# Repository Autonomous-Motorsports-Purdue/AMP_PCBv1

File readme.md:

PCB Documentation

	- H-bridge
		- An H-bridge is made up of four MOSFETs and four diodes.
		- It switches motor direction based on which two MOSFETs are on.
		- The diodes serve to allow reverse current from the motor to be released.
		- The current solution is Adafruit DRV8871.
			- Its current Limit is 3.6 Amps.
			- This is not enough for the brake Linear Actuator.
		- Recommend switching from DRV8871 to MCP1407.
		- Has peak current capability of 6 A, which is enough for the braking actuator.
		- https://ww1.microchip.com/downloads/en/DeviceDoc/20002019C.pdf
			
	- Steering PWM
		- A square wave is sent to input A of the servo.
		- The pulse width determines position of servo.
		
	- Differential Amplifier 
		- 
		- The formula for a voltage divider is V = VR + (R3/R1)(V1 - V2).
		- The circuit amplifies the difference between the two inputs and adds the voltage VR as an offset.
		- Amplifier for PCB needs to change 0.55 V to 0 V, and  2.75 to 12 volts.
		- Diagram for Reference: https://www.electronicshub.org/wp-content/uploads/2015/01/1.-Differential-amplifier-circuit.jpg
		
	- Braking Linear Actuator
		- 5 Amp Max Current Draw at 12 Volts
		- Duty Cycle: 5 minutes on, 15 minutes off
		- Speed of 1.38 in/s with load of 35 lbs

		Changes
			-C1, C3, C4 backwards footprints (non-polarized capacitors
			-Resistor footprints larger
			-

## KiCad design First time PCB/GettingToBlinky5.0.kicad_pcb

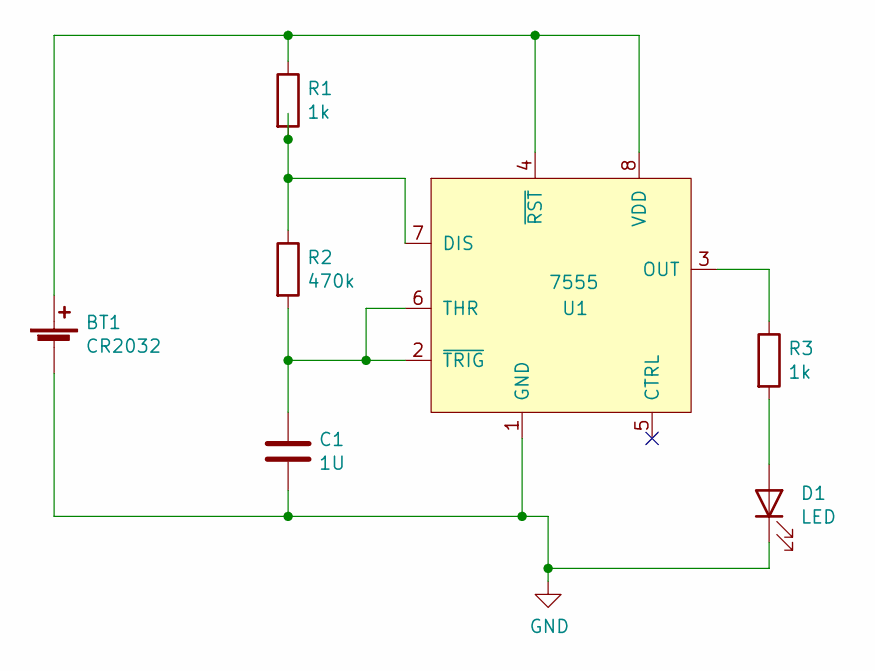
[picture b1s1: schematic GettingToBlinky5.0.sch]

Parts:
BT1: CR2032; S8211-46R
C1: 1U; C_0805_2012Metric_Pad1.15x1.40mm_HandSolder
D1: LED; LED_0805_2012Metric_Pad1.15x1.40mm_HandSolder
R1, R3: 1k; R_0805_2012Metric_Pad1.15x1.40mm_HandSolder
R2: 470k; R_0805_2012Metric_Pad1.15x1.40mm_HandSolder
U1: 7555; SOIC-8_3.9x4.9mm_P1.27mm

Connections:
GND: BT1.2 (-), C1.2, D1.1 (K), U1.1 (GND)
unnamed: BT1.1 (+), R1.1, U1.4 (~RST), U1.8 (VDD)
unnamed: C1.1, R2.2, U1.2 (~TRIG), U1.6 (THR)
unnamed: D1.2 (A), R3.2
unnamed: R1.2, R2.1, U1.7 (DIS)
unnamed: R3.1, U1.3 (OUT)

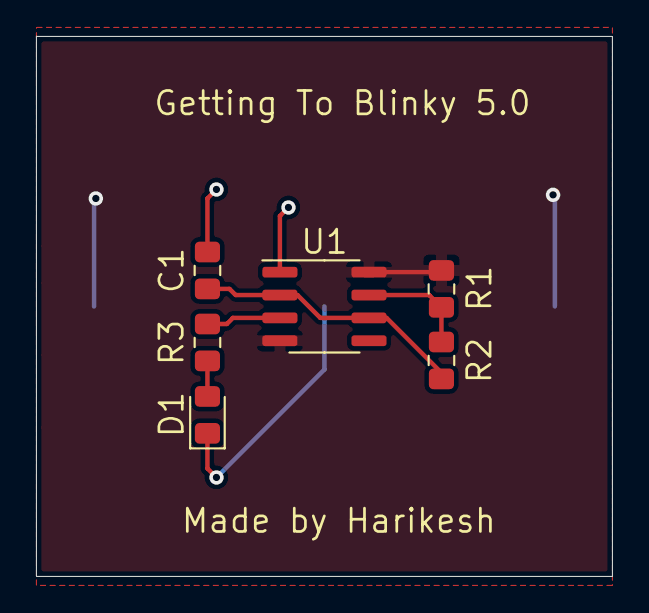
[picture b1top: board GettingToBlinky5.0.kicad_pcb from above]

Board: 2 copper layers, 32.0 x 30.0 mm, 7 parts (1 on the bottom side), 6 nets.

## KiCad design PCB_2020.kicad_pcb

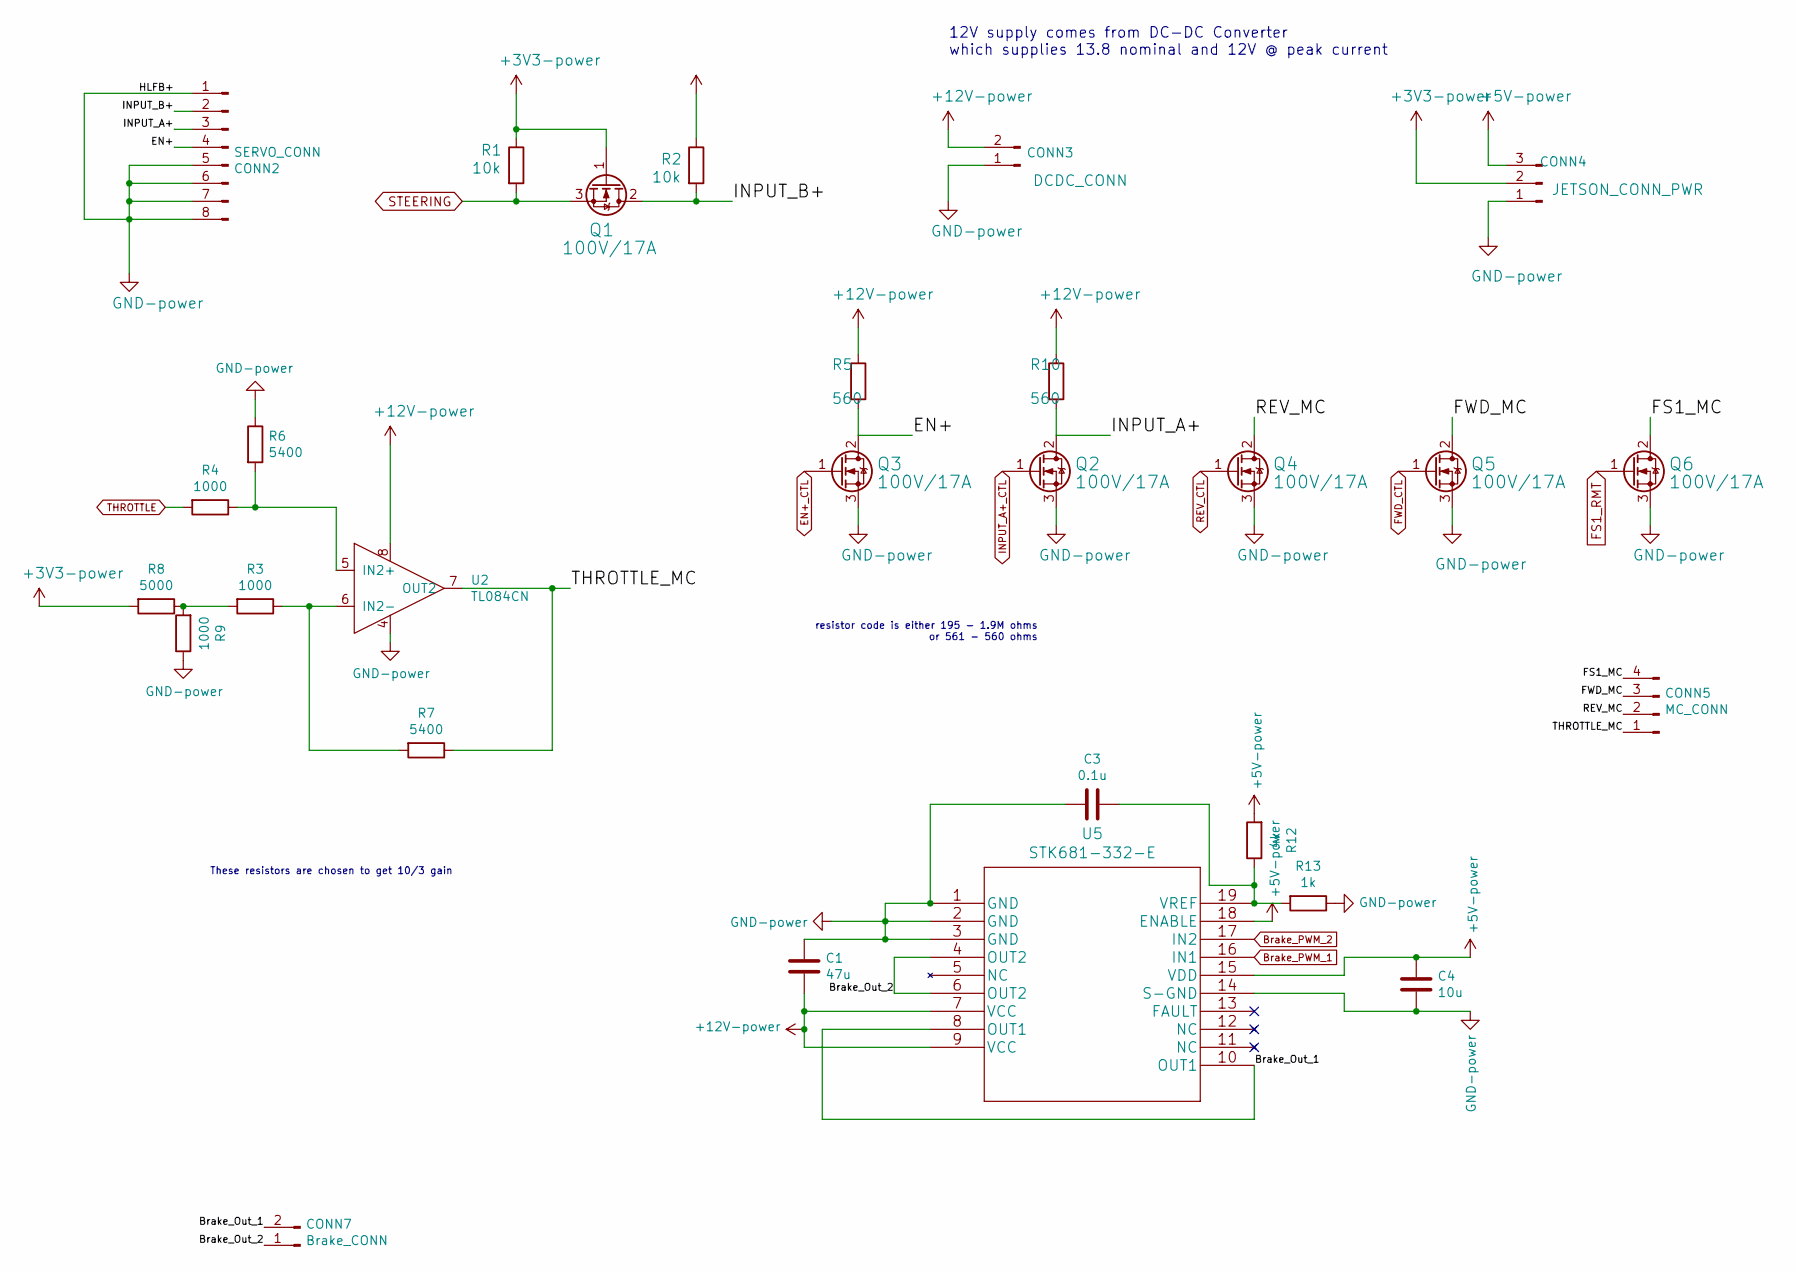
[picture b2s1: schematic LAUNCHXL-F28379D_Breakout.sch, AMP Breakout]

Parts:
C1: 47u; C_Radial_D4.0mm_H5.0mm_P1.50mm
C3: 0.1u; CP_Radial_D4.0mm_P1.50mm
C4: 10u; CP_Radial_D4.0mm_P1.50mm
CONN2: SERVO_CONN; Molex_Mini-Fit_Jr_5566-08A_2x04_P4.20mm_Vertical
CONN5: MC_CONN; Molex_KK-254_AE-6410-04A_1x04_P2.54mm_Vertical
CONN7: Brake_CONN; Molex_Mini-Fit_Jr_5566-02A_2x01_P4.20mm_Vertical
DCDC_CONN_12V: DCDC_CONN; Molex_Mini-Fit_Jr_5566-02A_2x01_P4.20mm_Vertical
JETSON_CONN_PWR: JETSON_CONN_PWR; Molex_KK-254_AE-6410-03A_1x03_P2.54mm_Vertical
Q1, Q2, Q3, Q4, Q5, Q6: 100V/17A; TO-220-3_Vertical
R1, R2: 10k; R_Axial_DIN0204_L3.6mm_D1.6mm_P7.62mm_Horizontal
R3, R4, R9: 1000; R_Axial_DIN0204_L3.6mm_D1.6mm_P7.62mm_Horizontal
R5, R18: 560; R_Axial_DIN0204_L3.6mm_D1.6mm_P7.62mm_Horizontal
R6, R7: 5400; R_Axial_DIN0204_L3.6mm_D1.6mm_P7.62mm_Horizontal
R8: 5000; R_Axial_DIN0204_L3.6mm_D1.6mm_P7.62mm_Horizontal
R12: 4k; R_Axial_DIN0204_L3.6mm_D1.6mm_P7.62mm_Horizontal
R13: 1k; R_Axial_DIN0204_L3.6mm_D1.6mm_P7.62mm_Horizontal
U2: TL084CN
U5: STK681-332-E

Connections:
+3V3: Q1.1 (G), R1.1, R8.2; also elsewhere on the board
+5V: C4.2, R12.2, U5.15 (VDD), U5.18 (ENABLE); also elsewhere on the board
+12V: C1.1, R2.1, R5.1, U2.8, U5.7 (VCC), U5.9 (VCC); also elsewhere on the board
/LAUNCHXL-F28379D Breakout/Brake_Out_1: CONN7.2, U5.8 (OUT1), U5.10 (OUT1)
/LAUNCHXL-F28379D Breakout/Brake_Out_2: CONN7.1, U5.4 (OUT2), U5.6 (OUT2)
/LAUNCHXL-F28379D Breakout/EN+: CONN2.4, Q3.2 (D), R5.2
/LAUNCHXL-F28379D Breakout/FS1_MC: CONN5.4, Q6.2 (D)
/LAUNCHXL-F28379D Breakout/FWD_MC: CONN5.3, Q5.2 (D)
/LAUNCHXL-F28379D Breakout/INPUT_A+: CONN2.3, Q2.2 (D); also elsewhere on the board
/LAUNCHXL-F28379D Breakout/INPUT_B+: CONN2.2, Q1.2 (D), R2.2
/LAUNCHXL-F28379D Breakout/REV_MC: CONN5.2, Q4.2 (D)
/LAUNCHXL-F28379D Breakout/THROTTLE_MC: CONN5.1, R7.1, U2.7 (OUT2)
Brake_PWM_1: U5.16 (IN1); also elsewhere on the board
Brake_PWM_2: U5.17 (IN2); also elsewhere on the board
EN+_CTL: Q3.1 (G); also elsewhere on the board
FS1_RMT: Q6.1 (G); also elsewhere on the board
FWD_CTL: Q5.1 (G); also elsewhere on the board
GND: C1.2, C3.1, C4.1, CONN2.1, CONN2.5, CONN2.6, CONN2.7, CONN2.8, Q2.3 (S), Q3.3 (S), Q4.3 (S), Q5.3 (S), Q6.3 (S), R6.1, R9.1, R13.1, U2.4, U5.1 (GND), U5.2 (GND), U5.3 (GND), U5.14 (S-GND); also elsewhere on the board
INPUT_A+_CTL: Q2.1 (G); also elsewhere on the board
unnamed: C3.2, R12.1, R13.2, U5.19 (VREF)
unnamed: R3.1, R7.2, U2.6 (IN2-)
unnamed: R3.2, R8.1, R9.2
unnamed: R4.1, R6.2, U2.5 (IN2+)
REV_CTL: Q4.1 (G); also elsewhere on the board
STEERING: Q1.3 (S), R1.2; also elsewhere on the board
THROTTLE: R4.2; also elsewhere on the board

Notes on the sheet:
12V supply comes from DC-DC Converter which supplies 13.8 nominal and 12V @ peak current
resistor code is either 195 - 1.9M ohms or 561 - 560 ohms
These resistors are chosen to get 10/3 gain

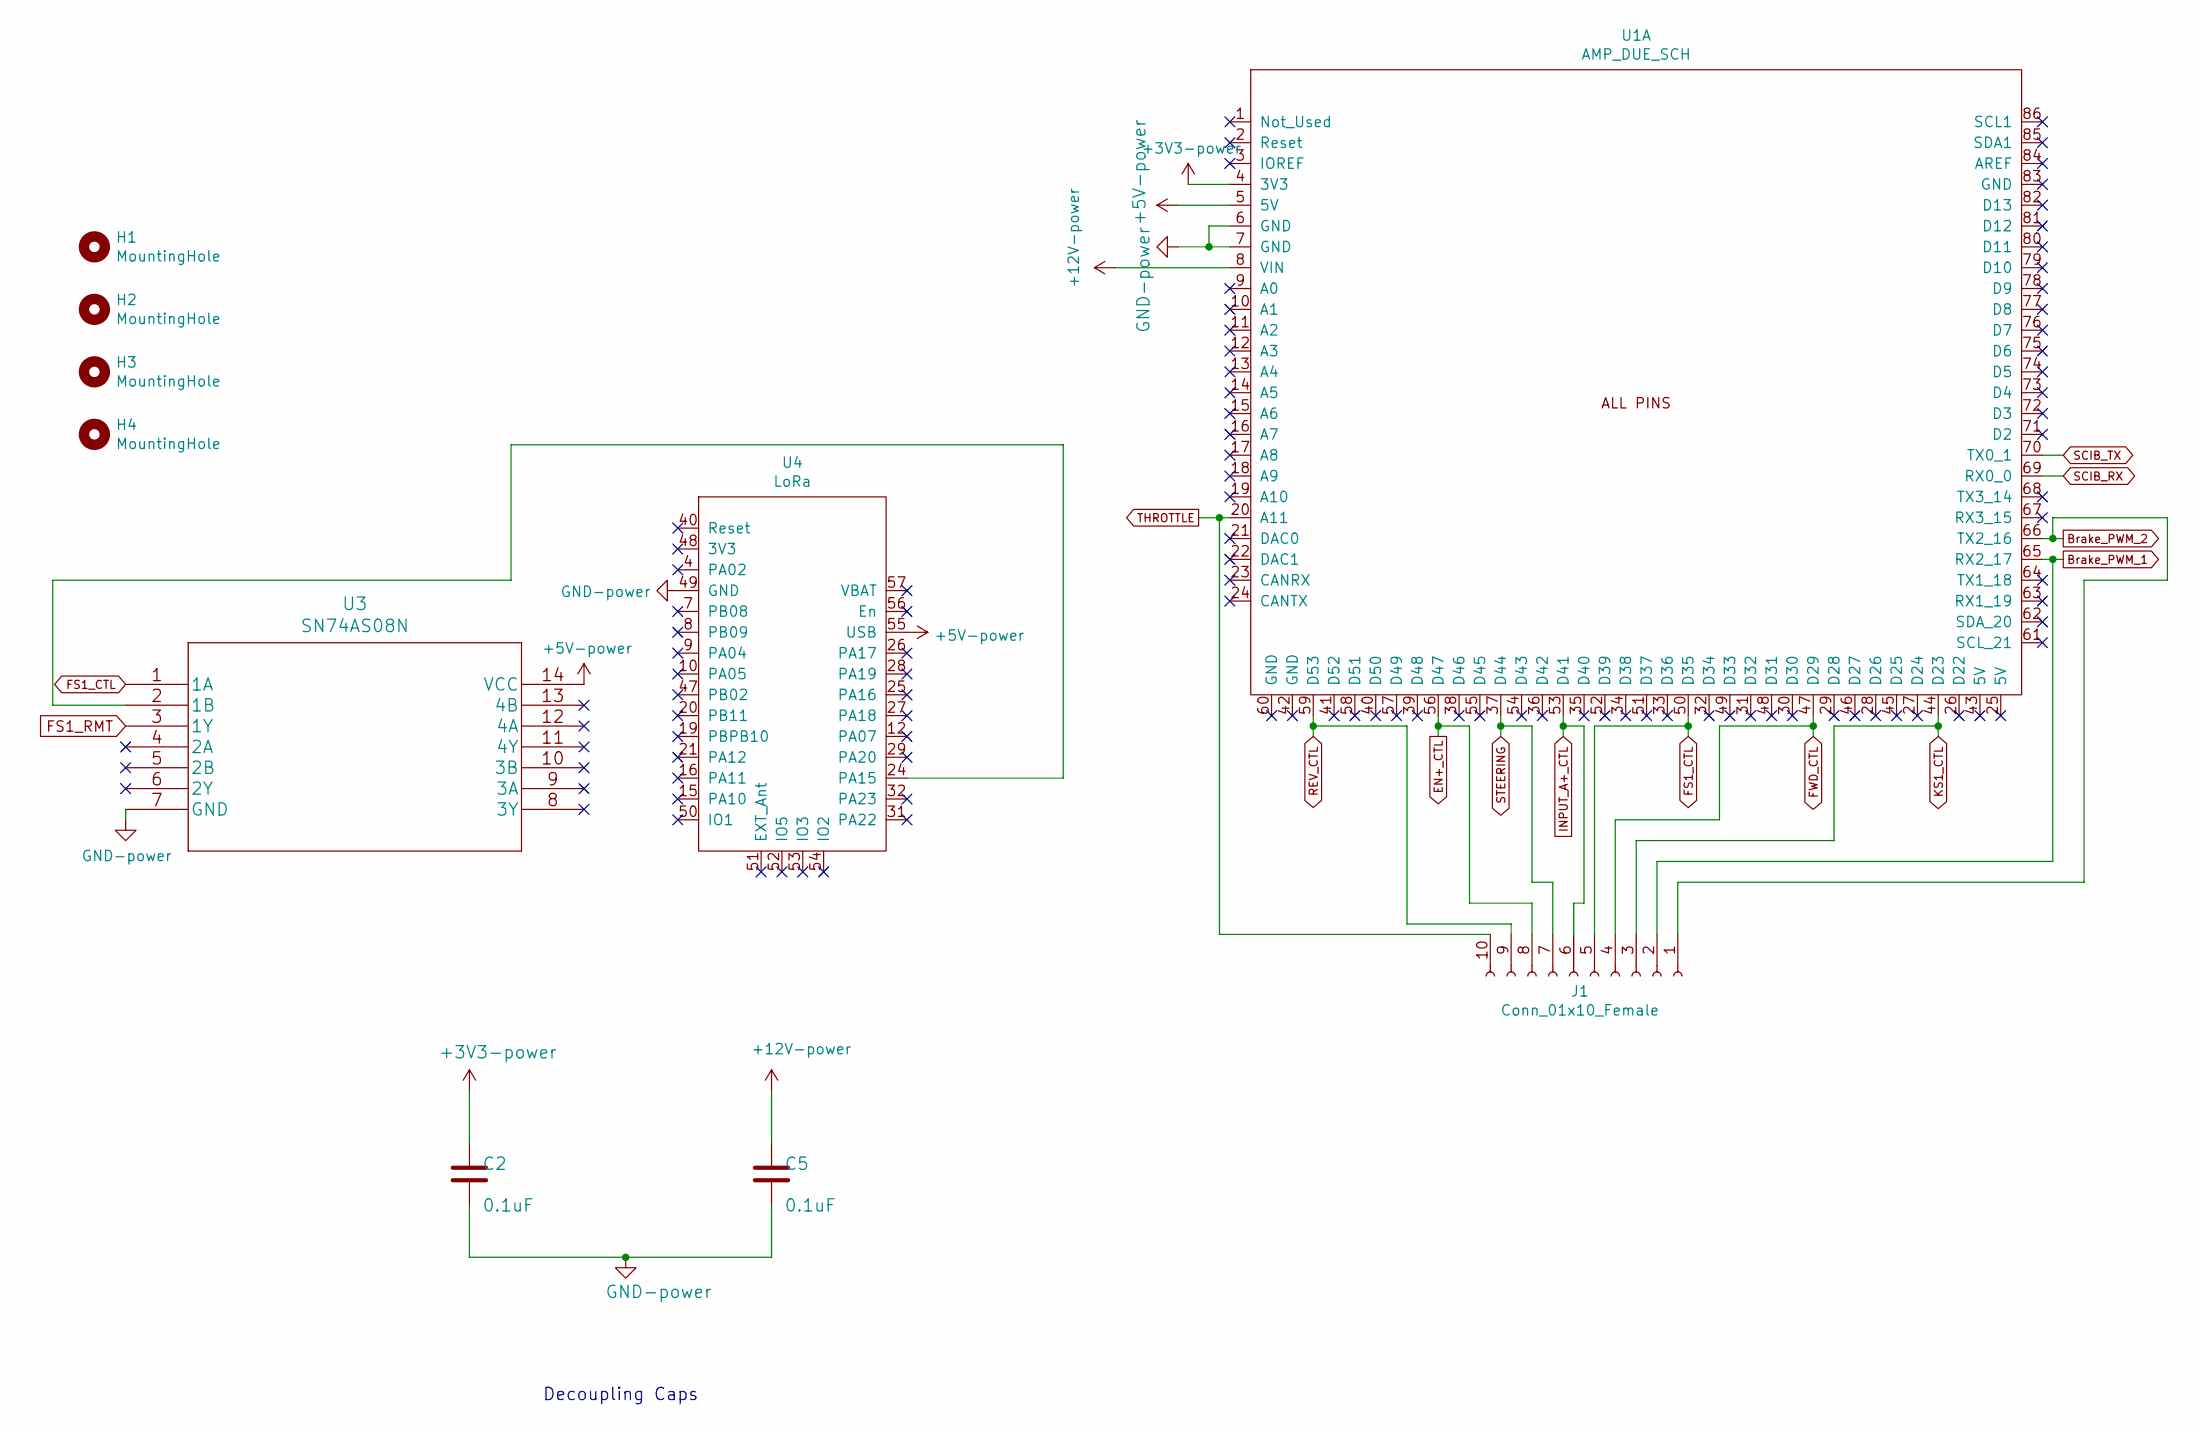
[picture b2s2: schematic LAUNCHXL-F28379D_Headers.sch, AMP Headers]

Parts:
C2, C5: 0.1uF; CP_Radial_D4.0mm_P1.50mm
H1, H2, H3, H4: MountingHole; MountingHole_2.7mm
J1: Conn_01x10_Female; Molex_Mini-Fit_Jr_5566-10A2_2x05_P4.20mm_Vertical
U1: AMP_DUE_SCH; Arduino DUE
U3: SN74AS08N
U4: LoRa

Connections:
+3V3: C2.1, U1.4 (3V3); also elsewhere on the board
+5V: U1.5 (5V), U3.14 (VCC), U4.55 (USB); also elsewhere on the board
+12V: C5.1, U1.8 (VIN); also elsewhere on the board
Brake_PWM_1: J1.2, U1.65 (RX2_17); also elsewhere on the board
Brake_PWM_2: J1.1, U1.66 (TX2_16); also elsewhere on the board
EN+_CTL: J1.8, U1.56 (D47); also elsewhere on the board
FS1_CTL: J1.5, U1.50 (D35), U3.1 (1A)
FS1_RMT: U3.3 (1Y); also elsewhere on the board
FWD_CTL: J1.4, U1.47 (D29); also elsewhere on the board
GND: C2.2, C5.2, U1.6 (GND), U1.7 (GND), U3.7 (GND), U4.49 (GND); also elsewhere on the board
INPUT_A+_CTL: J1.6, U1.53 (D41); also elsewhere on the board
KS1_CTL: J1.3, U1.44 (D23)
unnamed: U3.2 (1B), U4.24 (PA15)
REV_CTL: J1.9, U1.59 (D53); also elsewhere on the board
SCIB_RX: U1.69 (RX0_0)
SCIB_TX: U1.70 (TX0_1)
STEERING: J1.7, U1.37 (D44); also elsewhere on the board
THROTTLE: J1.10, U1.20 (A11); also elsewhere on the board

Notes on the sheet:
Decoupling Caps

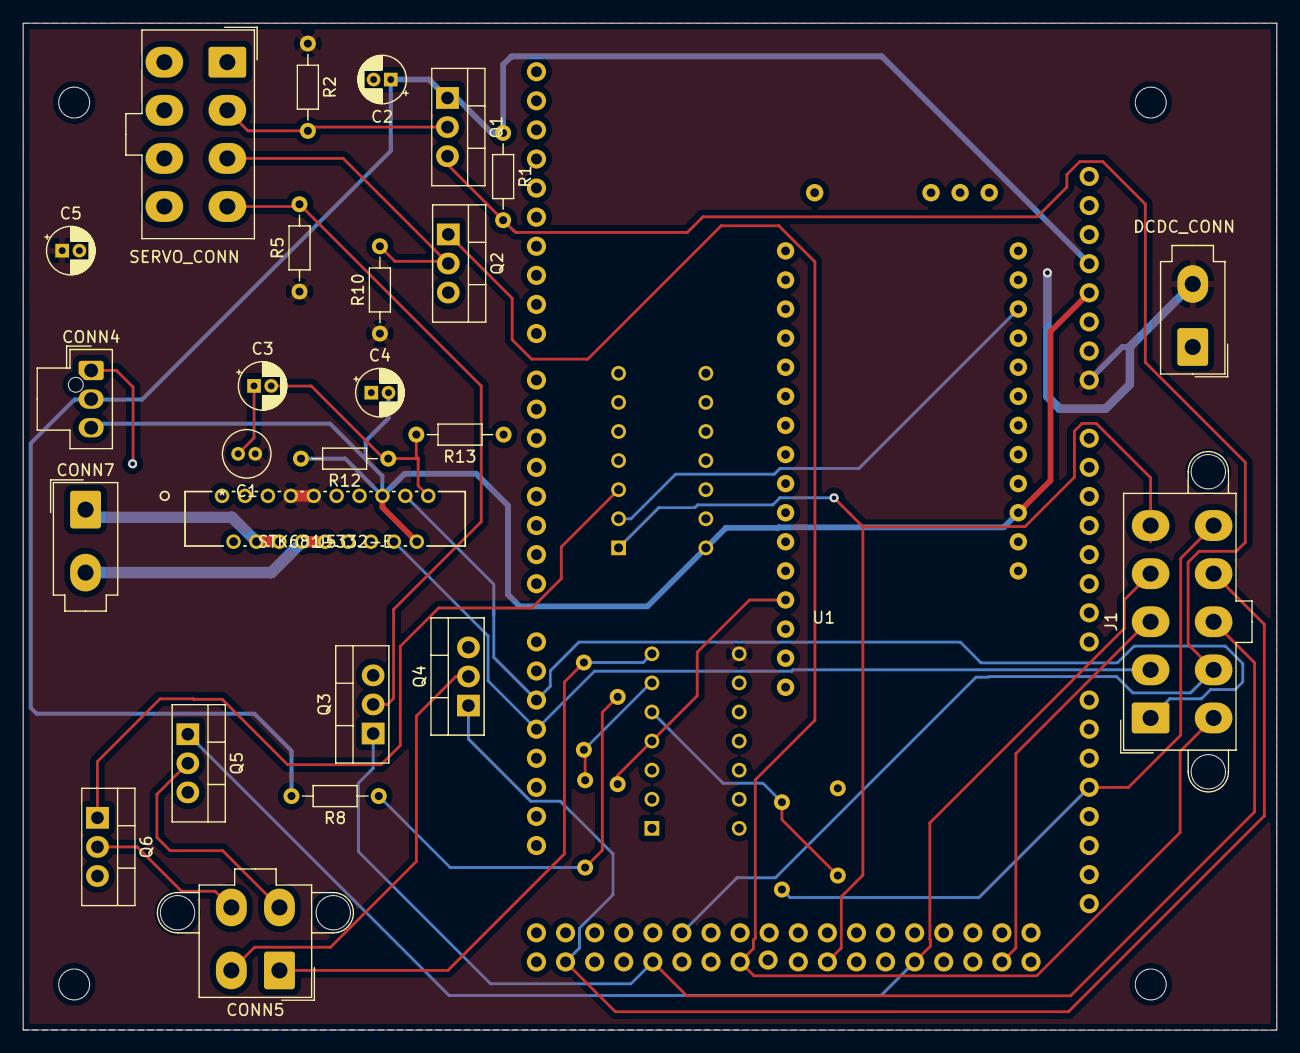
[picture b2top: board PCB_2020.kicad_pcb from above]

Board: 2 copper layers, 109.5 x 87.9 mm, 38 parts (0 on the bottom side), 29 nets.

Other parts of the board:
CONN3: DCDC_CONN; Molex_Mini-Fit_Jr_5566-02A_2x01_P4.20mm_Vertical
CONN4: JETSON_CONN_PWR; Molex_Nano-Fit_105309-xx03_1x03_P2.50mm_Vertical
R10: 560; R_Axial_DIN0204_L3.6mm_D1.6mm_P7.62mm_Horizontal

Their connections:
+3V3: CONN4.2; also elsewhere on the board
+5V: CONN4.3; also elsewhere on the board
+12V: CONN3.2, R10.1; also elsewhere on the board
/LAUNCHXL-F28379D Breakout/INPUT_A+: R10.2; also elsewhere on the board
GND: CONN3.1, CONN4.1; also elsewhere on the board

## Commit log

2020-09-20 Worked on H-Bridge and Linear Actuator
2020-09-21 Monday 9/21
2020-09-22 Tuesday 9/22
2020-09-23 Adding KiCad Tutorial and Updated Readme
2020-09-23 Test commit document
2020-09-23 Edited text in test file
2020-09-28 added to gerbers for pos layouts
2020-09-29 My gerber files for the blinky tutorial
2020-09-29 Working on Diff Amp Simulation in KiCad
2020-09-29 Updated Readme.md to reflect new information
2020-10-06 Working on KiCad Simulation
2020-10-06 Updated Differential Section of readme
2020-10-06 Working on Diff Simulator
2020-10-10 Working on Diff Simulator Bugs
2020-10-10 Mitch updated diff amp sim files
2020-10-11 LTSpice Simulation
2020-10-13 Added GettingToBlinky PCB
2020-10-13 LTSpice Simulation Finished
2020-10-13 updated pcb
2020-10-19 Updating PCB
2020-10-20 Reworked PCB
2020-10-27 Changed to diff op amp with single sided supply
2020-10-27 First commit for Arduino Pinout
2020-11-03 Final Arduino Pinout Schematic
2020-11-10 Added feather LoRa pinout
2020-11-11 Working on PCB Routing for LoRa
2020-11-25 Updating PCB with LoRa
2021-01-17 Added AND gate for Feather LoRa, and changed over to through hole components
2021-03-25 updated PCB with bluetooth connector for arduino signals
2021-09-20 'updated files'
2021-09-27 updated 3d models for pcb items
2021-09-27 updated pcb models
2021-09-28 deleted tutorial folder
2021-10-18 updated trace width
2021-10-18 updated motor driver connections
2021-10-18 updated design rules
2021-10-23 changed connectors to be all Molex

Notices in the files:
parts and their libraries:
Copyright 2016 Accelerated Designs. All rights reserved.
